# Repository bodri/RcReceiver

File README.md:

# RcReceiver
RC Receiver using redundant SX1280 modules.

[Firmware can de found here](https://github.com/bodri/rc-receiver-sx1280)

# Why SX1280?
Mostly high end RC transmitters/receivers are using the good old CC2500 chipset. Also when you hear SX1280 probably the first word pops in your mind is LoRa. At the same time SX1280 chip also supports FLRC mode which is very similar to MSK used on CC2500, but according to the documentation SX1280 does it with 16 dBm higher receiver sensitivity at ~250kBaud data rate with FEC.

I have a Weatronic BAT 60 and a Jeti DS-24 transmitter, so I tested my first [prototype](https://www.instructables.com/id/High-Resolution-PWM-Signal-Generation-for-RC-Servo/) of this SX1280 radio against them. I tested them in an urban area around my house, and I can already tell you the DS-24 lost the signal first (3-4 houses down the street) and then BAT 60 and way later my SX1280 radio. My prototype used a single SX1280 module. In this project I would like to build a receiver and transmitter module with redundant SX120 modules.

I hope very soon I can make some real line of sight tests. (Note that I'm living in the Netherlands so it's a challenge).

# Status (April 13, 2019)
* The PCB has an error: unfortunately, the TXB0108 pins are mixed in the KiCad standard library, so the PWM output cannot be used
* The silkscreen for the RF modules are mixed
* Both RF module work
* Serial ports (S1, GPS), Analog port (An) and the CAN interface is not tested yet

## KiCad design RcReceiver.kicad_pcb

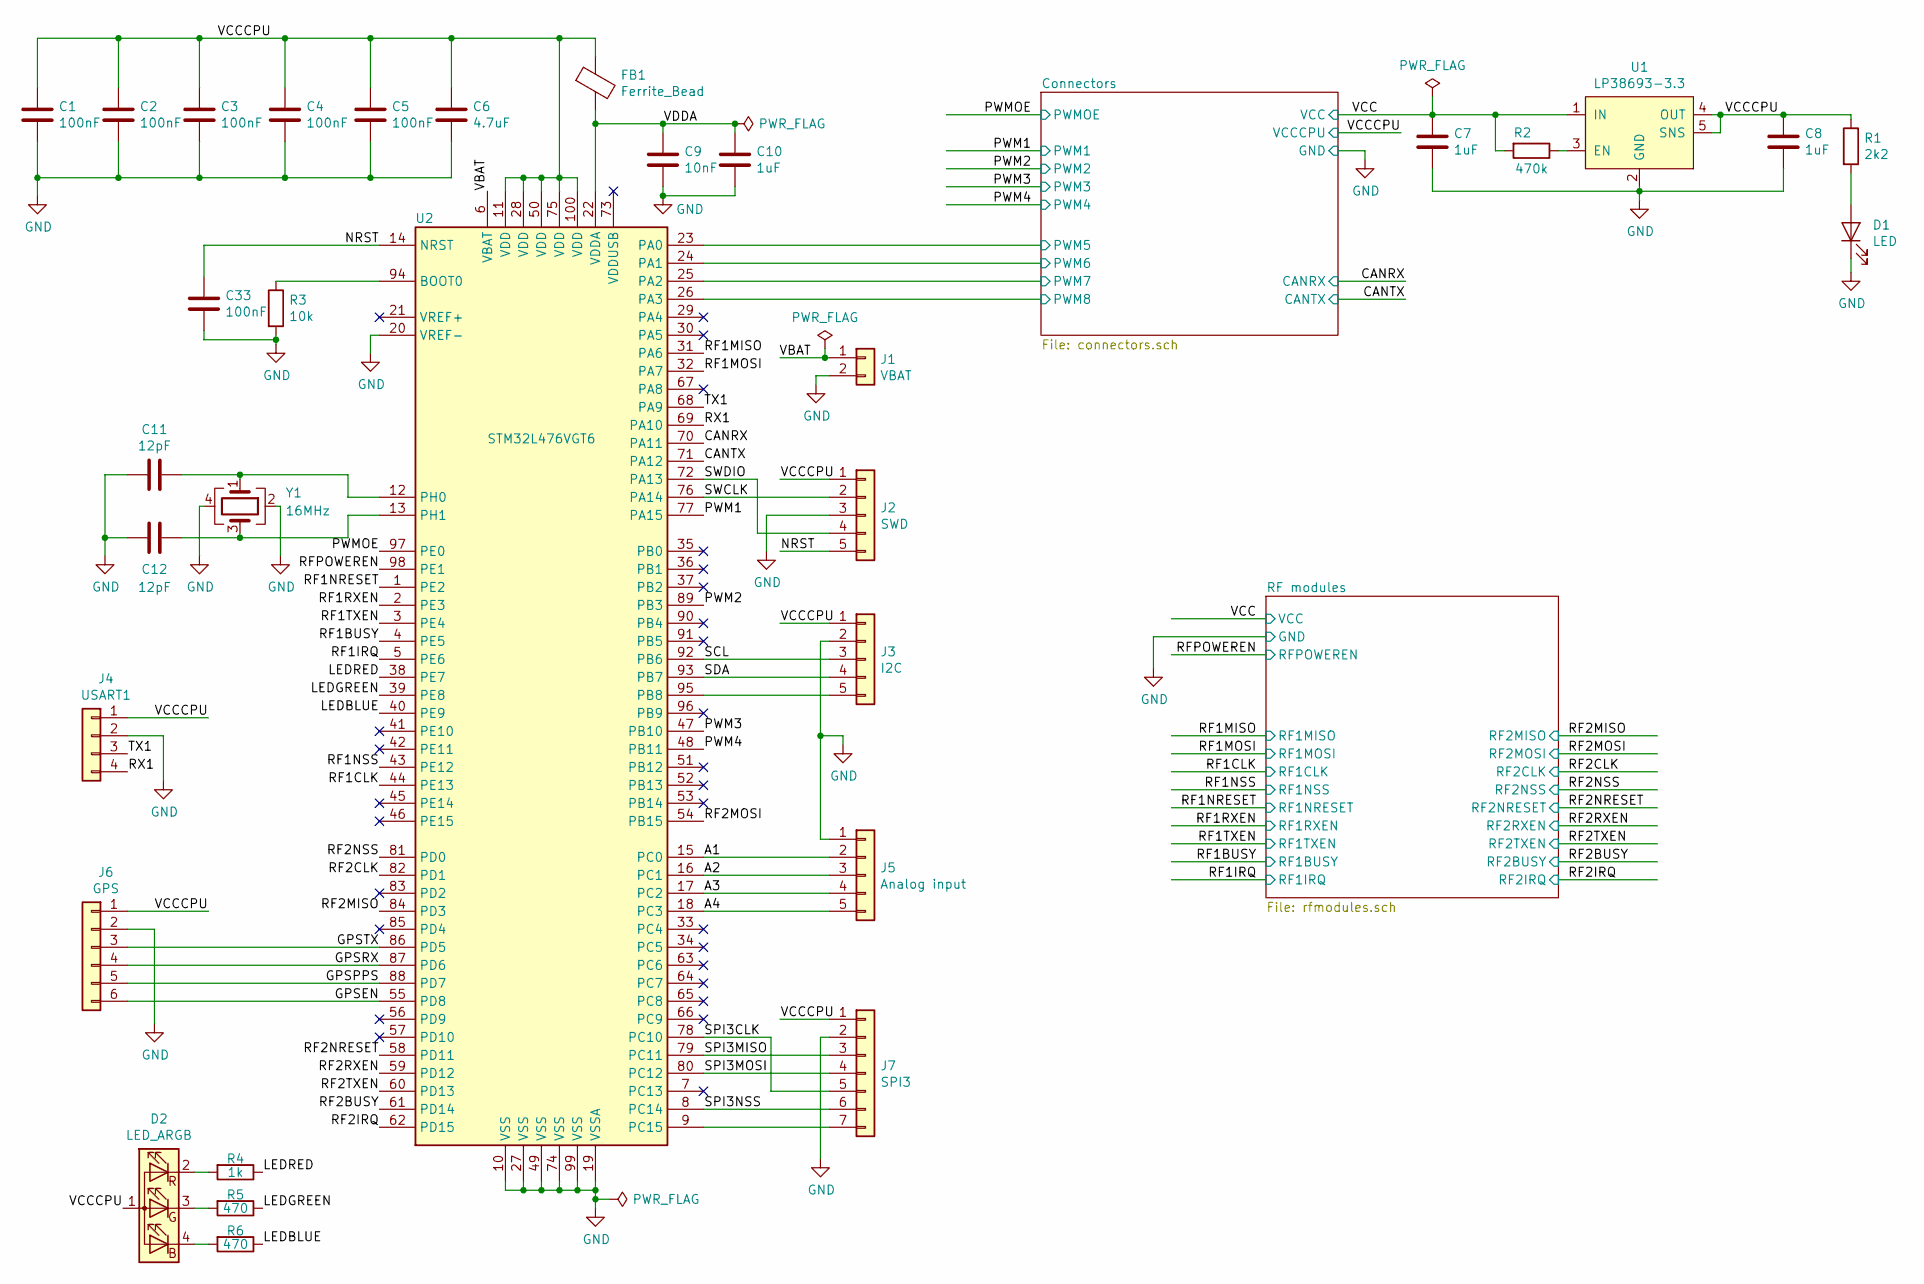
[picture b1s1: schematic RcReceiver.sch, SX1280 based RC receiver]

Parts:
C1, C2, C3, C4, C5, C33: 100nF; C_0402_1005Metric
C6: 4.7uF; C_0402_1005Metric
C7, C8, C10: 1uF; C_0402_1005Metric
C9: 10nF; C_0402_1005Metric
C11, C12: 12pF; C_0402_1005Metric
D1: LED; LED_0402_1005Metric
D2: LED_ARGB; LED_Lumex-LX0404
FB1: Ferrite_Bead; L_0402_1005Metric
J1: VBAT; PinHeader_1x02_P1.27mm_Vertical
J2: SWD; JST_SH_BM05B-SRSS-TB_1x05-1MP_P1.00mm_Vertical
J3: I2C; JST_SH_BM05B-SRSS-TB_1x05-1MP_P1.00mm_Vertical
J4: USART1; JST_SH_BM04B-SRSS-TB_1x04-1MP_P1.00mm_Vertical
J5: Analog input; JST_SH_BM05B-SRSS-TB_1x05-1MP_P1.00mm_Vertical
J6: GPS; JST_SH_BM06B-SRSS-TB_1x06-1MP_P1.00mm_Vertical
J7: SPI3; JST_SH_BM07B-SRSS-TB_1x07-1MP_P1.00mm_Vertical
R1: 2k2; R_0402_1005Metric
R2: 470k; R_0402_1005Metric
R3: 10k; R_0402_1005Metric
R4: 1k; R_0402_1005Metric
R5, R6: 470; R_0402_1005Metric
U1: LP38693-3.3; WSON-6_3x3mm_Pitch0.95mm
U2: STM32L476VGT6; LQFP-100_14x14mm_P0.5mm
Y1: 16MHz; Oscillator_SMD_SeikoEpson_SG210-4Pin_2.5x2.0mm

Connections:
/A1: J5.2, U2.15 (PC0)
/A2: J5.3, U2.16 (PC1)
/A3: J5.4, U2.17 (PC2)
/A4: J5.5, U2.18 (PC3)
/CANRX: U2.70 (PA11); also elsewhere on the board
/CANTX: U2.71 (PA12); also elsewhere on the board
/Connectors/PWM5: U2.23 (PA0); also elsewhere on the board
/Connectors/PWM6: U2.24 (PA1); also elsewhere on the board
/Connectors/PWM7: U2.25 (PA2); also elsewhere on the board
/Connectors/PWM8: U2.26 (PA3); also elsewhere on the board
/GPSEN: J6.6, U2.55 (PD8)
/GPSPPS: J6.5, U2.88 (PD7)
/GPSRX: J6.4, U2.87 (PD6)
/GPSTX: J6.3, U2.86 (PD5)
/LEDBLUE: R6.1, U2.40 (PE9)
/LEDGREEN: R5.1, U2.39 (PE8)
/LEDRED: R4.1, U2.38 (PE7)
/NRST: C33.1, J2.5, U2.14 (NRST)
/PWM1: U2.77 (PA15); also elsewhere on the board
/PWM2: U2.89 (PB3); also elsewhere on the board
/PWM3: U2.47 (PB10); also elsewhere on the board
/PWM4: U2.48 (PB11); also elsewhere on the board
/PWMOE: U2.97 (PE0); also elsewhere on the board
/RF1BUSY: U2.4 (PE5); also elsewhere on the board
/RF1CLK: U2.44 (PE13); also elsewhere on the board
/RF1IRQ: U2.5 (PE6); also elsewhere on the board
/RF1MISO: U2.31 (PA6); also elsewhere on the board
/RF1MOSI: U2.32 (PA7); also elsewhere on the board
/RF1NRESET: U2.1 (PE2); also elsewhere on the board
/RF1NSS: U2.43 (PE12); also elsewhere on the board
/RF1RXEN: U2.2 (PE3); also elsewhere on the board
/RF1TXEN: U2.3 (PE4); also elsewhere on the board
/RF2BUSY: U2.61 (PD14); also elsewhere on the board
/RF2CLK: U2.82 (PD1); also elsewhere on the board
/RF2IRQ: U2.62 (PD15); also elsewhere on the board
/RF2MISO: U2.84 (PD3); also elsewhere on the board
/RF2MOSI: U2.54 (PB15); also elsewhere on the board
/RF2NRESET: U2.58 (PD11); also elsewhere on the board
/RF2NSS: U2.81 (PD0); also elsewhere on the board
/RF2RXEN: U2.59 (PD12); also elsewhere on the board
/RF2TXEN: U2.60 (PD13); also elsewhere on the board
/RFPOWEREN: U2.98 (PE1); also elsewhere on the board
/RX1: J4.4, U2.69 (PA10)
/SCL: J3.3, U2.92 (PB6)
/SDA: J3.4, U2.93 (PB7)
/SPI3CLK: J7.5, U2.78 (PC10)
/SPI3MISO: J7.3, U2.79 (PC11)
/SPI3MOSI: J7.4, U2.80 (PC12)
/SPI3NSS: J7.6, U2.8 (PC14)
/SWCLK: J2.2, U2.76 (PA14)
/SWDIO: J2.4, U2.72 (PA13)
/TX1: J4.3, U2.68 (PA9)
/VBAT: J1.1, U2.6 (VBAT)
/VCCCPU: C1.1, C2.1, C3.1, C4.1, C5.1, C6.1, C8.1, D2.1 (A), FB1.1, J2.1, J3.1, J4.1, J6.1, J7.1, R1.1, U1.4 (OUT), U1.5 (SNS), U2.11 (VDD), U2.28 (VDD), U2.50 (VDD), U2.75 (VDD), U2.100 (VDD); also elsewhere on the board
/VDDA: C9.1, C10.1, FB1.2, U2.22 (VDDA)
GND: C1.2, C2.2, C3.2, C4.2, C5.2, C6.2, C7.2, C8.2, C9.2, C10.2, C11.2, C12.2, C33.2, D1.1 (K), J1.2, J2.3, J3.2, J4.2, J5.1, J6.2, J7.2, R3.2, U1.2 (GND), U1.7 (GND), U2.10 (VSS), U2.19 (VSSA), U2.20 (VREF-), U2.27 (VSS), U2.49 (VSS), U2.74 (VSS), U2.99 (VSS), Y1.2, Y1.4; also elsewhere on the board
IN: C7.1, R2.2, U1.1 (IN), U1.6 (IN); also elsewhere on the board
unnamed: C11.1, U2.12 (PH0), Y1.1
unnamed: C12.1, U2.13 (PH1), Y1.3
unnamed: D1.2 (A), R1.2
unnamed: D2.2 (RK), R4.2
unnamed: D2.3 (GK), R5.2
unnamed: D2.4 (BK), R6.2
unnamed: J3.5, U2.95 (PB8)
unnamed: J7.7, U2.9 (PC15)
unnamed: R2.1, U1.3 (EN)
unnamed: R3.1, U2.94 (BOOT0)

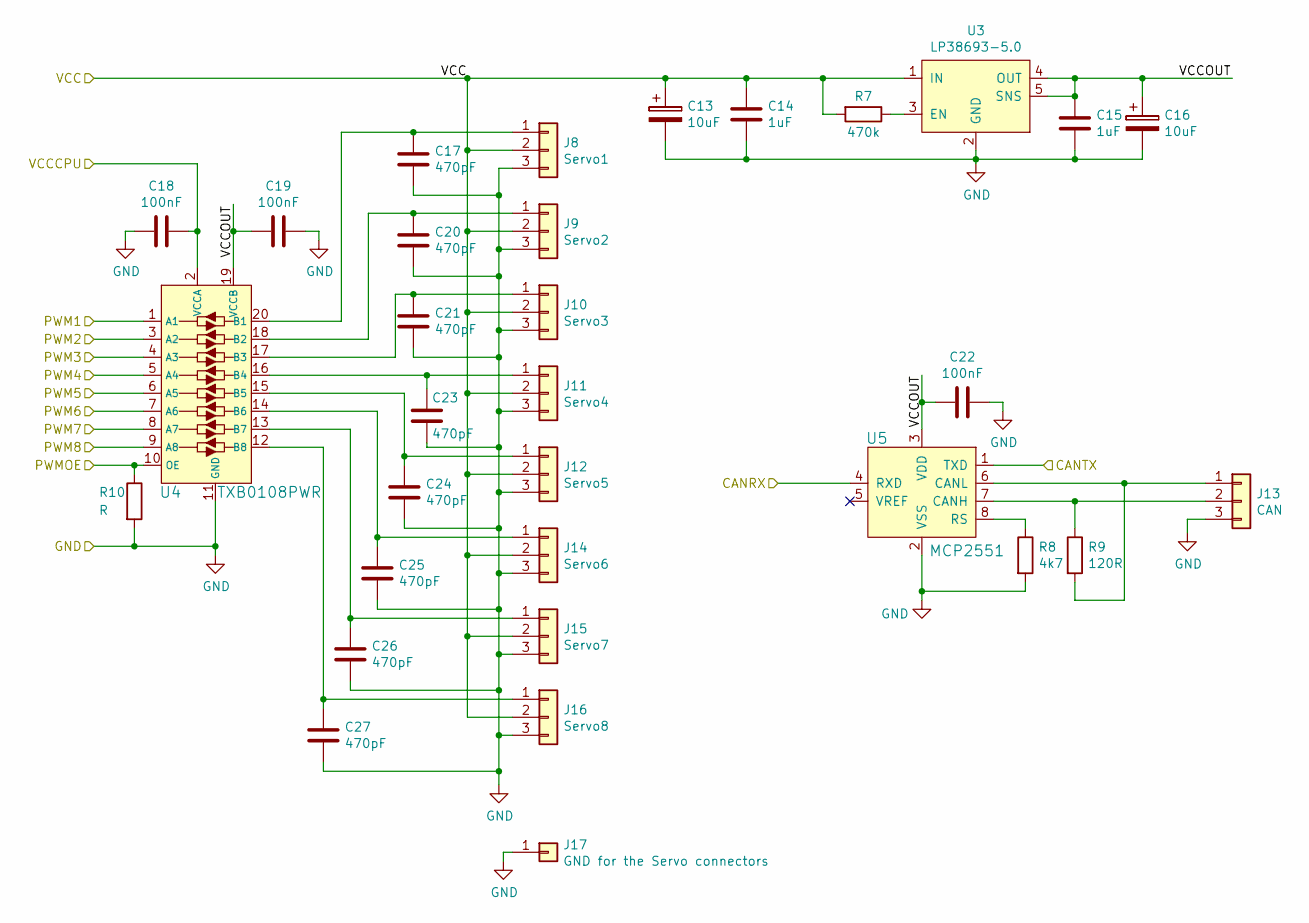
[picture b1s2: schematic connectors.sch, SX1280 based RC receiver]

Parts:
C13, C16: 10uF; CP_EIA-3216-18_Kemet-A
C14, C15: 1uF; C_0402_1005Metric
C17, C20, C21, C23, C24, C25, C26, C27: 470pF; C_0402_1005Metric
C18, C19, C22: 100nF; C_0402_1005Metric
J8: Servo1; PinHeader_1x03_P1.27mm_Side
J9: Servo2; PinHeader_1x03_P1.27mm_Side
J10: Servo3; PinHeader_1x03_P1.27mm_Side
J11: Servo4; PinHeader_1x03_P1.27mm_Side
J12: Servo5; PinHeader_1x03_P1.27mm_Side
J13: CAN; JST_SH_BM03B-SRSS-TB_1x03-1MP_P1.00mm_Vertical
J14: Servo6; PinHeader_1x03_P1.27mm_Side
J15: Servo7; PinHeader_1x03_P1.27mm_Side
J16: Servo8; PinHeader_1x03_P1.27mm_Side
J17: GND for the Servo connectors; PinHeader_1x01_P2.54mm_Vertical
R7: 470k; R_0402_1005Metric
R8: 4k7; R_0402_1005Metric
R9: 120R; R_0402_1005Metric
R10: R; R_0402_1005Metric
U3: LP38693-5.0; WSON-6_3x3mm_Pitch0.95mm
U4: TXB0108PWR; TSSOP-20_W4.4mm; MPN TXB0108PWR; Digi-Key_PN 296-21527-1-ND
U5: MCP2551; SOIC-8_W3.9mm; MPN MCP2551-I/SN; Digi-Key_PN MCP2551-I/SN-ND

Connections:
/CANRX: U5.4 (RXD); also elsewhere on the board
/CANTX: U5.1 (TXD); also elsewhere on the board
/Connectors/PWM5: U4.6 (A5); also elsewhere on the board
/Connectors/PWM6: U4.7 (A6); also elsewhere on the board
/Connectors/PWM7: U4.8 (A7); also elsewhere on the board
/Connectors/PWM8: U4.9 (A8); also elsewhere on the board
/Connectors/VCCOUT: C15.1, C16.1, C19.2, C22.2, U3.4 (OUT), U3.5 (SNS), U4.19 (VCCB), U5.3 (VDD)
/PWM1: U4.1 (A1); also elsewhere on the board
/PWM2: U4.3 (A2); also elsewhere on the board
/PWM3: U4.4 (A3); also elsewhere on the board
/PWM4: U4.5 (A4); also elsewhere on the board
/PWMOE: R10.1, U4.10 (OE); also elsewhere on the board
/VCCCPU: C18.1, U4.2 (VCCA); also elsewhere on the board
GND: C13.2, C14.2, C15.2, C16.2, C17.2, C18.2, C19.1, C20.2, C21.2, C22.1, C23.2, C24.2, C25.2, C26.2, C27.2, J8.3, J9.3, J10.3, J11.3, J12.3, J13.3, J14.3, J15.3, J16.3, J17.1, R8.2, R10.2, U3.2 (GND), U3.7 (GND), U4.11 (GND), U5.2 (VSS); also elsewhere on the board
IN: C13.1, C14.1, J8.2, J9.2, J10.2, J11.2, J12.2, J14.2, J15.2, J16.2, R7.2, U3.1 (IN), U3.6 (IN); also elsewhere on the board
unnamed: C17.1, J8.1, U4.20 (B1)
unnamed 66: C20.1, J9.1, U4.18 (B2); also elsewhere on the board
unnamed: C21.1, J10.1, U4.17 (B3)
unnamed: C23.1, J11.1, U4.16 (B4)
unnamed: C24.1, J12.1, U4.15 (B5)
unnamed: C25.1, J14.1, U4.14 (B6)
unnamed: C26.1, J15.1, U4.13 (B7)
unnamed: C27.1, J16.1, U4.12 (B8)
unnamed: J13.1, R9.2, U5.6 (CANL)
unnamed: J13.2, R9.1, U5.7 (CANH)
unnamed: R7.1, U3.3 (EN)
unnamed: R8.1, U5.8 (RS)

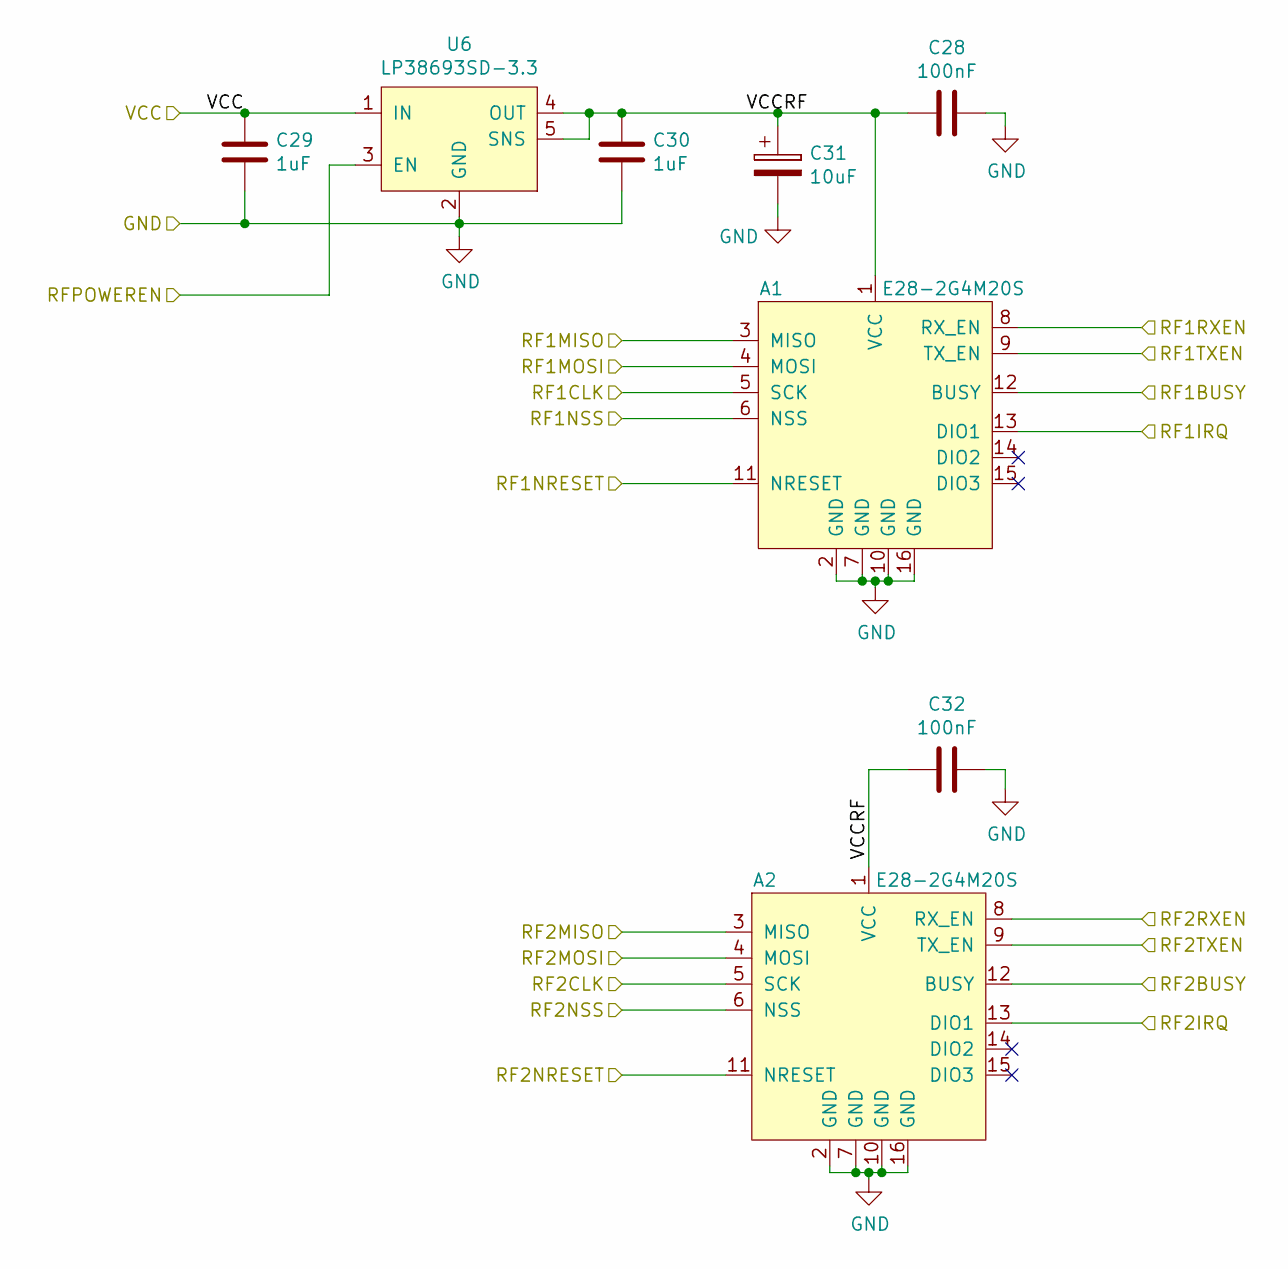
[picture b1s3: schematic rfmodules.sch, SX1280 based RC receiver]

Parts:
A1, A2: E28-2G4M20S
C28, C32: 100nF; C_0402_1005Metric
C29, C30: 1uF; C_0402_1005Metric
C31: 10uF; CP_EIA-3216-18_Kemet-A
U6: LP38693SD-3.3; WSON-6_3x3mm_Pitch0.95mm

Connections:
/RF1BUSY: A1.12 (BUSY); also elsewhere on the board
/RF1CLK: A1.5 (SCK); also elsewhere on the board
/RF1IRQ: A1.13 (DIO1); also elsewhere on the board
/RF1MISO: A1.3 (MISO); also elsewhere on the board
/RF1MOSI: A1.4 (MOSI); also elsewhere on the board
/RF1NRESET: A1.11 (NRESET); also elsewhere on the board
/RF1NSS: A1.6 (NSS); also elsewhere on the board
/RF1RXEN: A1.8 (RX_EN); also elsewhere on the board
/RF1TXEN: A1.9 (TX_EN); also elsewhere on the board
/RF2BUSY: A2.12 (BUSY); also elsewhere on the board
/RF2CLK: A2.5 (SCK); also elsewhere on the board
/RF2IRQ: A2.13 (DIO1); also elsewhere on the board
/RF2MISO: A2.3 (MISO); also elsewhere on the board
/RF2MOSI: A2.4 (MOSI); also elsewhere on the board
/RF2NRESET: A2.11 (NRESET); also elsewhere on the board
/RF2NSS: A2.6 (NSS); also elsewhere on the board
/RF2RXEN: A2.8 (RX_EN); also elsewhere on the board
/RF2TXEN: A2.9 (TX_EN); also elsewhere on the board
/RF modules/VCCRF: A1.1 (VCC), A2.1 (VCC), C28.2, C30.1, C31.1, C32.2, U6.4 (OUT), U6.5 (SNS)
/RFPOWEREN: U6.3 (EN); also elsewhere on the board
GND: A1.2 (GND), A1.7 (GND), A1.10 (GND), A1.16 (GND), A2.2 (GND), A2.7 (GND), A2.10 (GND), A2.16 (GND), C28.1, C29.2, C30.2, C31.2, C32.1, U6.2 (GND), U6.7 (GND); also elsewhere on the board
IN: C29.1, U6.1 (IN), U6.6 (IN); also elsewhere on the board

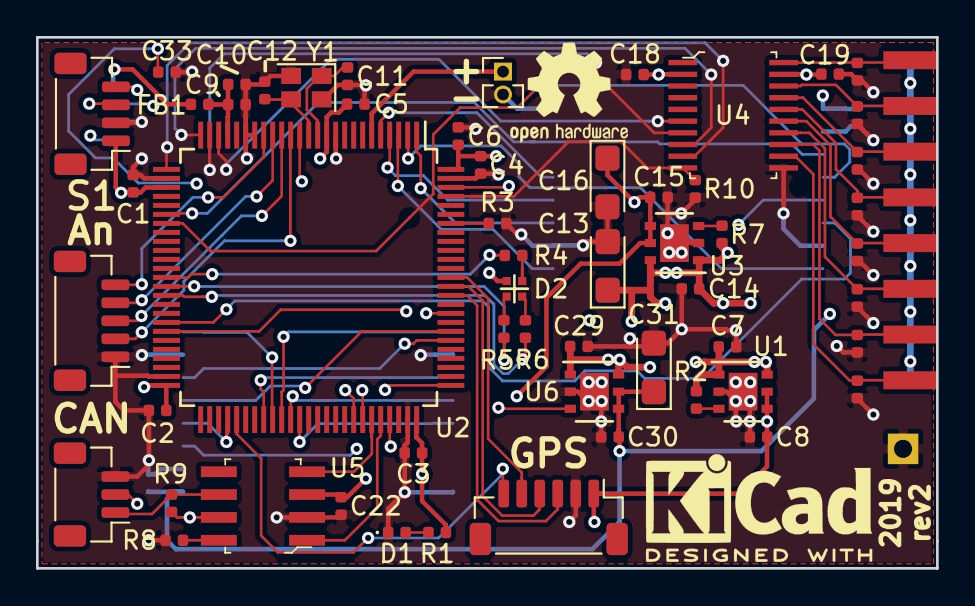
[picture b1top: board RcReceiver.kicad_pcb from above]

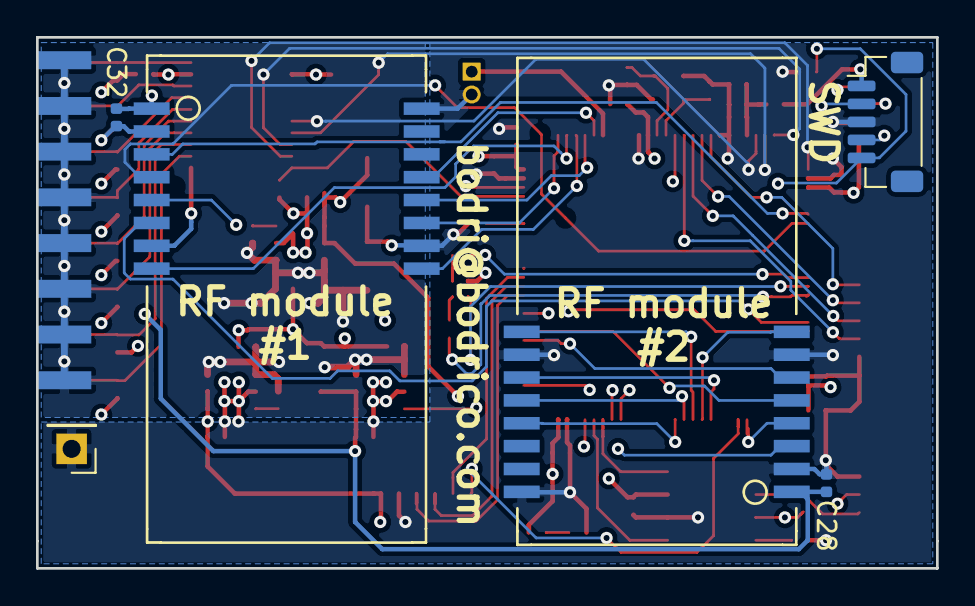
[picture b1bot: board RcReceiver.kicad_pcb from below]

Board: 4 copper layers, 50.0 x 29.5 mm, 72 parts (6 on the bottom side), 73 nets.

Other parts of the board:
KICADLOGO: KiCad-Logo2_6mm_SilkScreen
OSHLOGO: OSHW-Logo2_7.3x6mm_SilkScreen
wC20: 470pF; C_0402_1005Metric

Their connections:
GND: wC20.2; also elsewhere on the board
unnamed 66: wC20.1; also elsewhere on the board

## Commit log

2019-02-26 Add processor
2019-02-26 Fix typo
2019-02-27 Add LDO symbol
2019-02-27 Add connectors
2019-02-27 Add footprints
2019-02-27 Add missing pins and keep-out zone
2019-03-03 Add schema with RF modules
2019-03-03 Small changes
2019-03-07 Final changes in schema
2019-03-07 Add some footprints
2019-03-08 Create PCB
2019-03-09 Place all the components on the board
2019-03-14 Start routing
2019-03-14 Fix multiple REF problem
2019-03-15 More routing
2019-03-16 Routing finished
2019-03-16 Add fill zones
2019-04-11 Add some description
2019-04-13 Update status
2019-04-16 Change TBX0108 footprint
